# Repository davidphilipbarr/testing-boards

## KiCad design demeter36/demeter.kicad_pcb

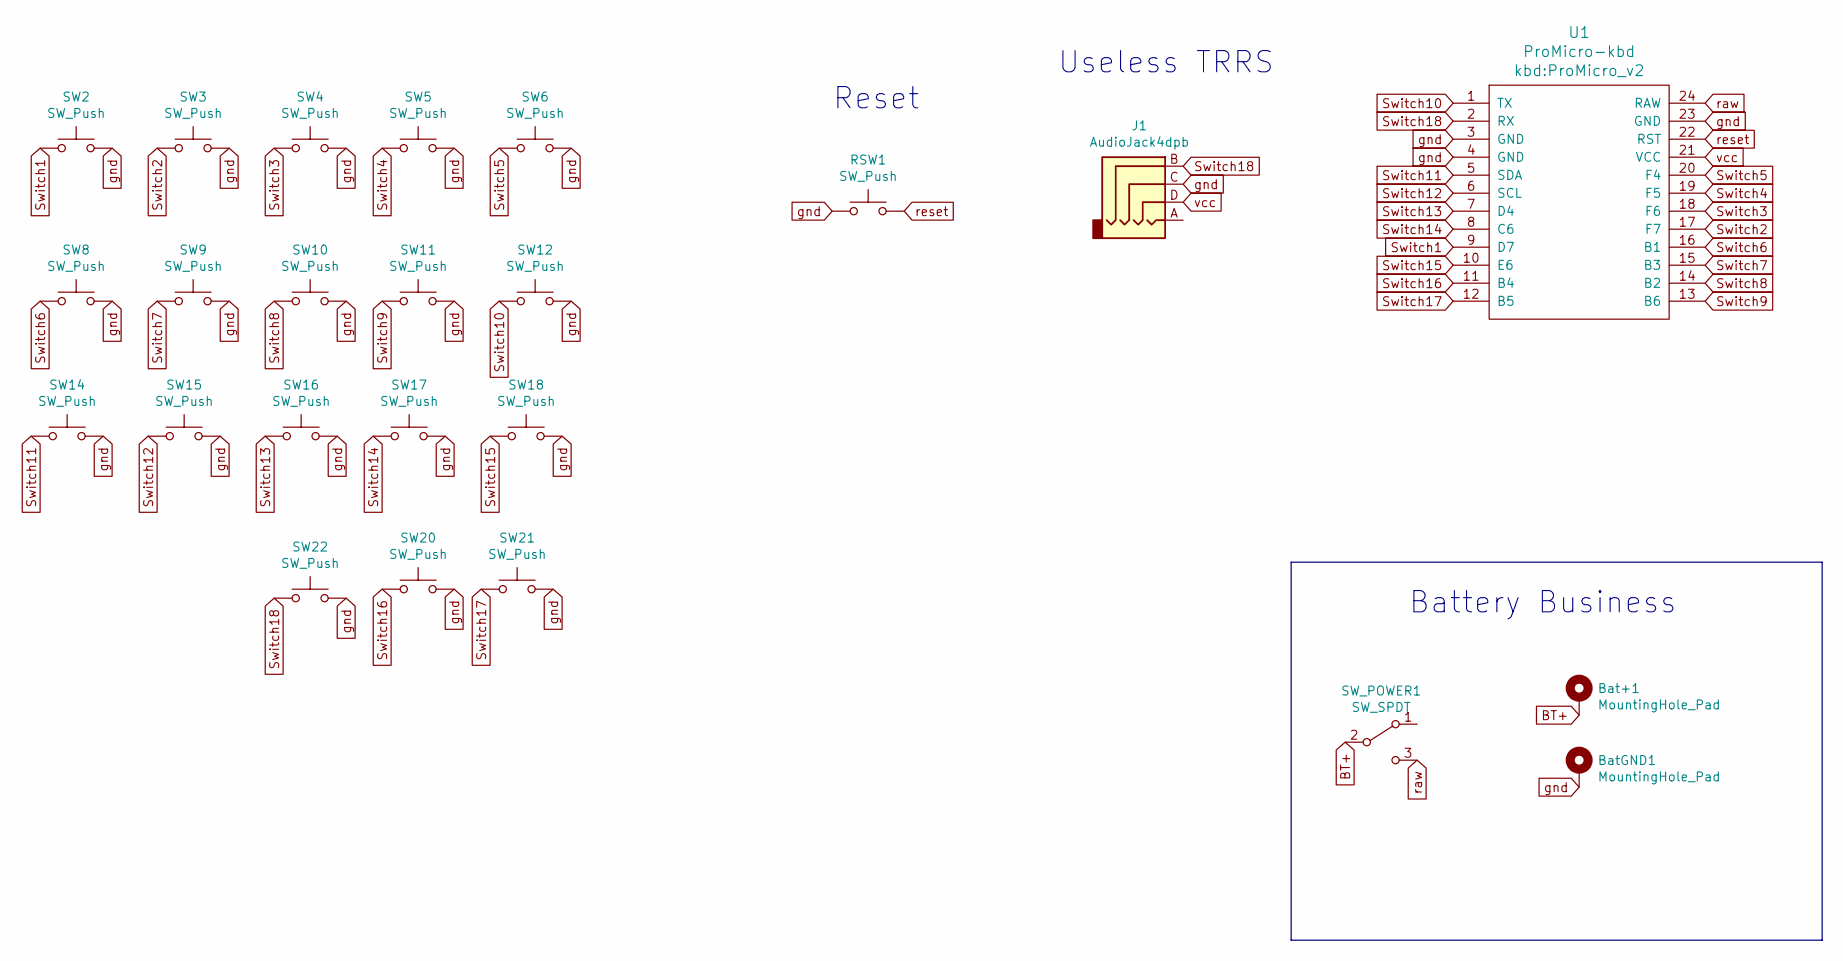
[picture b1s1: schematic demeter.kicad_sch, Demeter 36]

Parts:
Bat+1: MountingHole_Pad; 1pin_conn
BatGND1: MountingHole_Pad; 1pin_conn
J1: AudioJack4dpb; MJ-4PP-9
RSW1: SW_Push; ResetSW
SW2, SW3, SW4, SW5, SW6, SW8, SW9, SW10, SW11, SW12, SW14, SW15, SW16, SW17, SW18, SW20, SW21, SW22: SW_Push; SW_PG1350_rev_DPB
SW_POWER1: SW_SPDT; SPDT_C128955
U1: ProMicro-kbd; ProMicro_v2

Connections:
BT+: Bat+1.1, SW_POWER1.2 (B), U1.27; also elsewhere on the board
Switch1: SW2.1, U1.9 (D7)
Switch2: SW3.1, U1.17 (F7)
Switch3: SW4.1, U1.18 (F6)
Switch4: SW5.1, U1.19 (F5)
Switch5: SW6.1, U1.20 (F4)
Switch6: SW8.1, U1.16 (B1)
Switch7: SW9.1, U1.15 (B3)
Switch8: SW10.1, U1.14 (B2)
Switch9: SW11.1, U1.13 (B6)
Switch10: SW12.1, U1.1 (TX)
Switch11: SW14.1, U1.5 (SDA)
Switch12: SW15.1, U1.6 (SCL)
Switch13: SW16.1, U1.7 (D4)
Switch14: SW17.1, U1.8 (C6)
Switch15: SW18.1, U1.10 (E6)
Switch16: SW20.1, U1.11 (B4)
Switch17: SW21.1, U1.12 (B5)
Switch18: J1.B, SW22.1, U1.2 (RX); also elsewhere on the board
gnd: BatGND1.1, J1.C, RSW1.1, SW2.2, SW3.2, SW4.2, SW5.2, SW6.2, SW8.2, SW9.2, SW10.2, SW11.2, SW12.2, SW14.2, SW15.2, SW16.2, SW17.2, SW18.2, SW20.2, SW21.2, SW22.2, U1.3 (GND), U1.4 (GND), U1.23 (GND); also elsewhere on the board
raw: SW_POWER1.3 (C), U1.24 (RAW); also elsewhere on the board
reset: RSW1.2, U1.22 (RST)
vcc: J1.D, U1.21 (VCC)

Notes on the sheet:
Reset
Battery Business
Useless TRRS

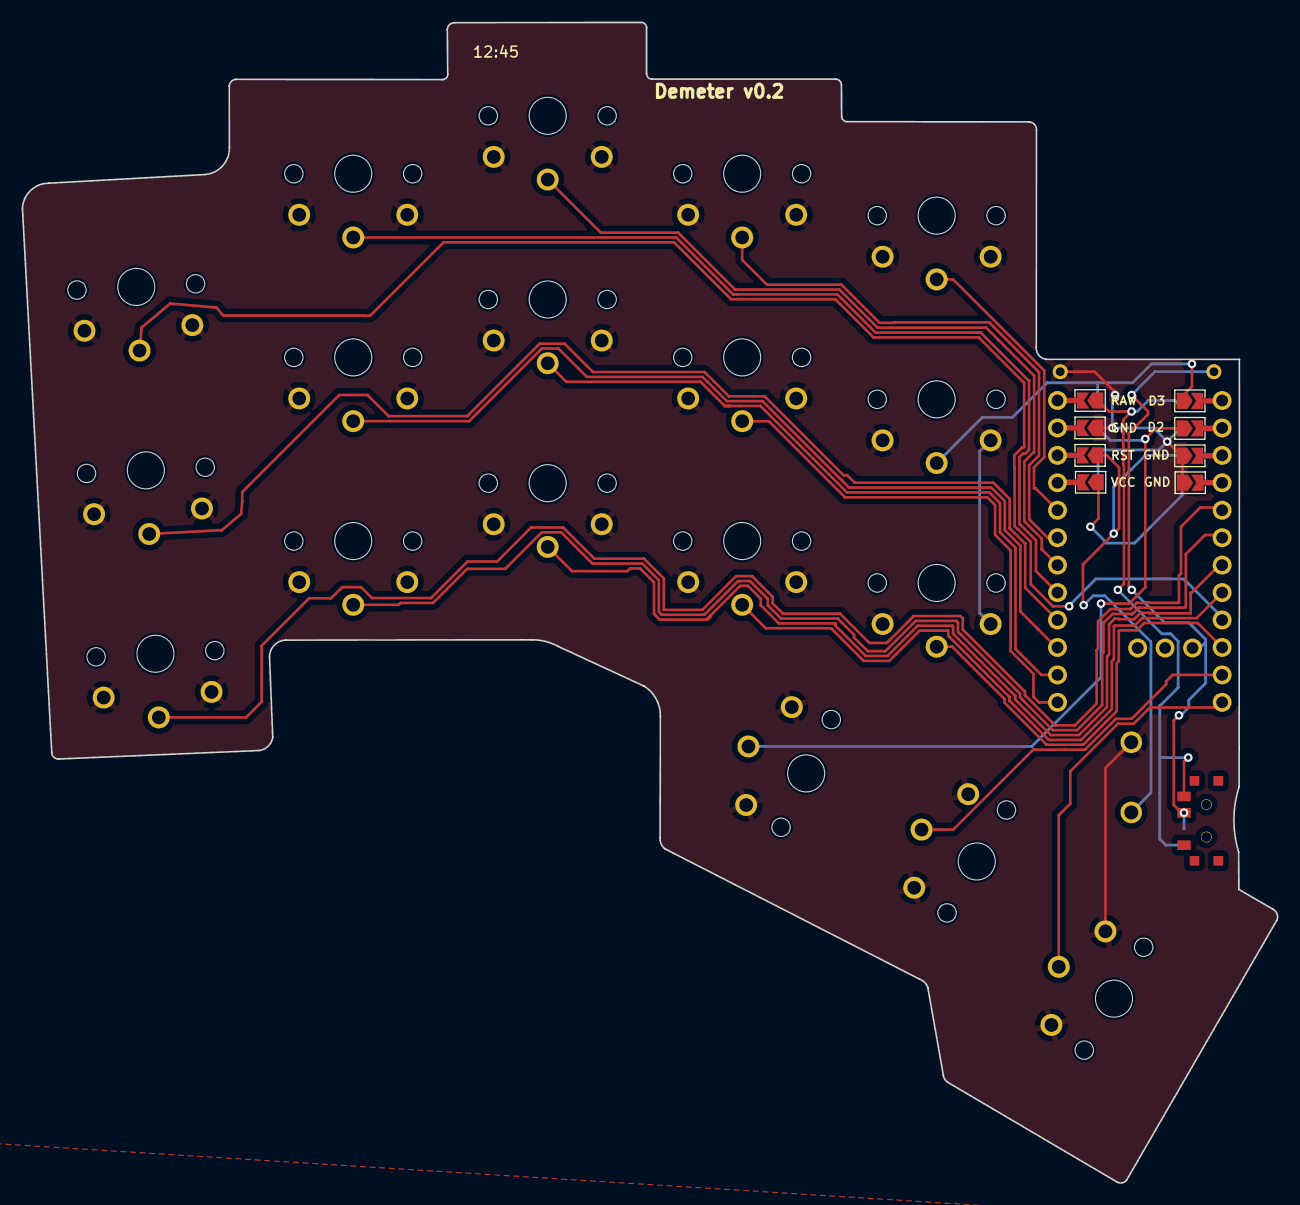
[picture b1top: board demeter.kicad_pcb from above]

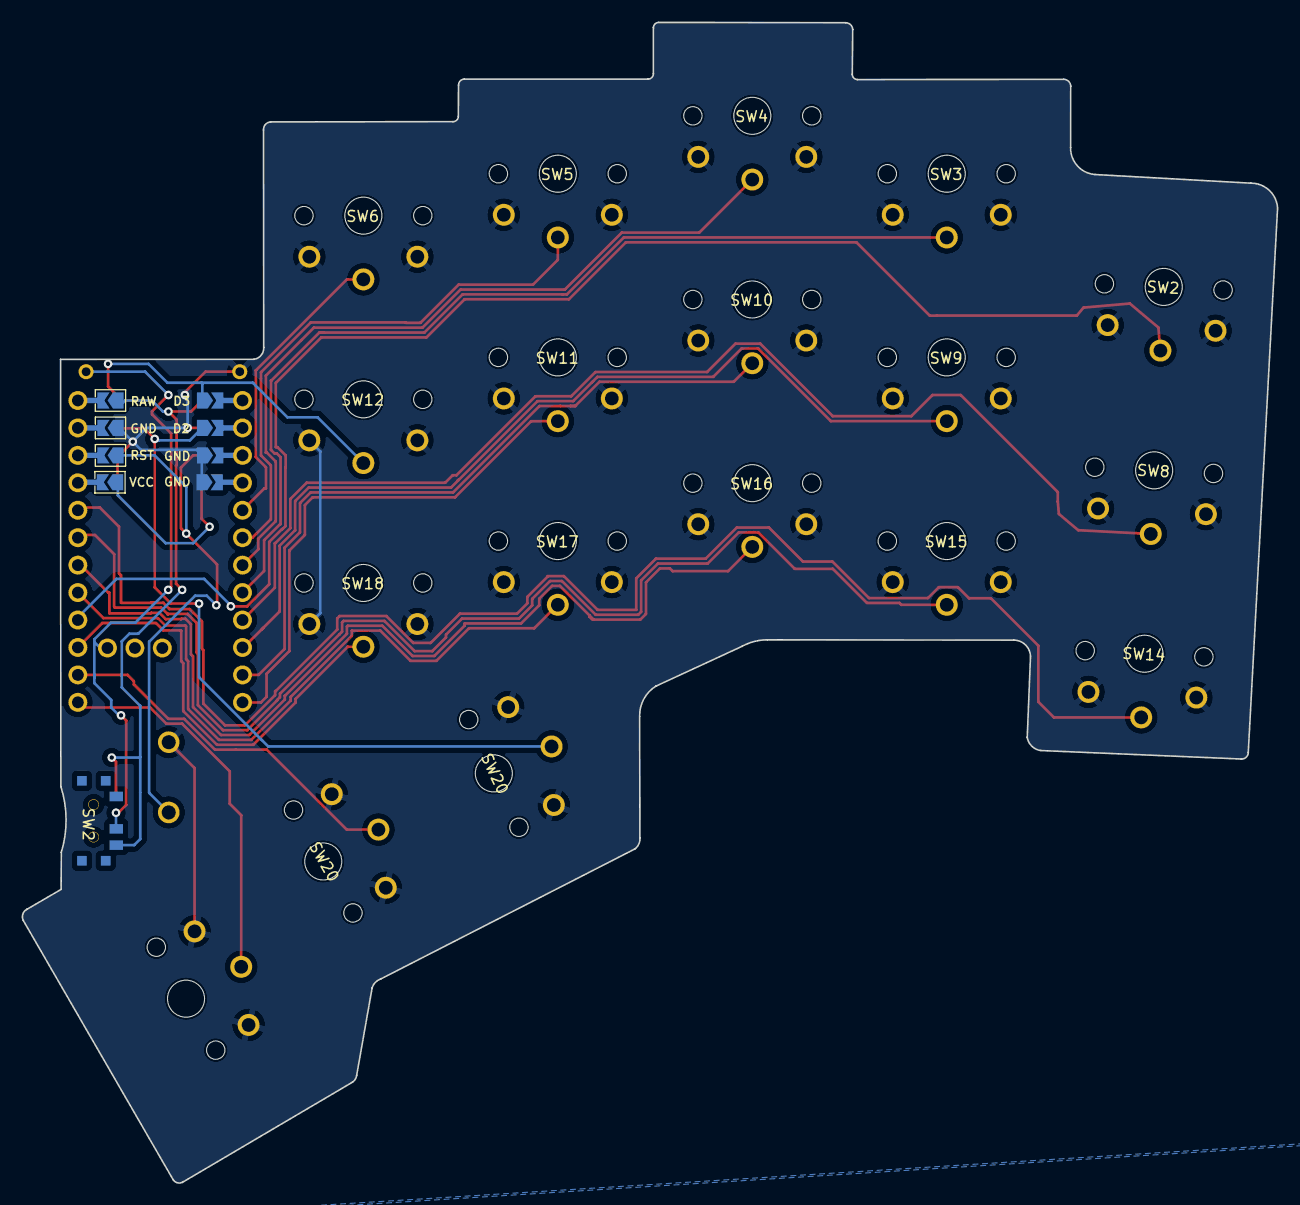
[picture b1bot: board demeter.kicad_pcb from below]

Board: 2 copper layers, 116.2 x 107.4 mm, 24 parts (2 on the bottom side), 22 nets.

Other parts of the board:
SW2#2: SW_SPDT; SPDT_C128955r
SW20#2: SW_Push; SW_PG1350_rev_DPB2.2

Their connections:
BT+: SW2#2.2; also elsewhere on the board
Switch18: SW20#2.1; also elsewhere on the board
gnd: SW20#2.2; also elsewhere on the board
raw: SW2#2.3; also elsewhere on the board

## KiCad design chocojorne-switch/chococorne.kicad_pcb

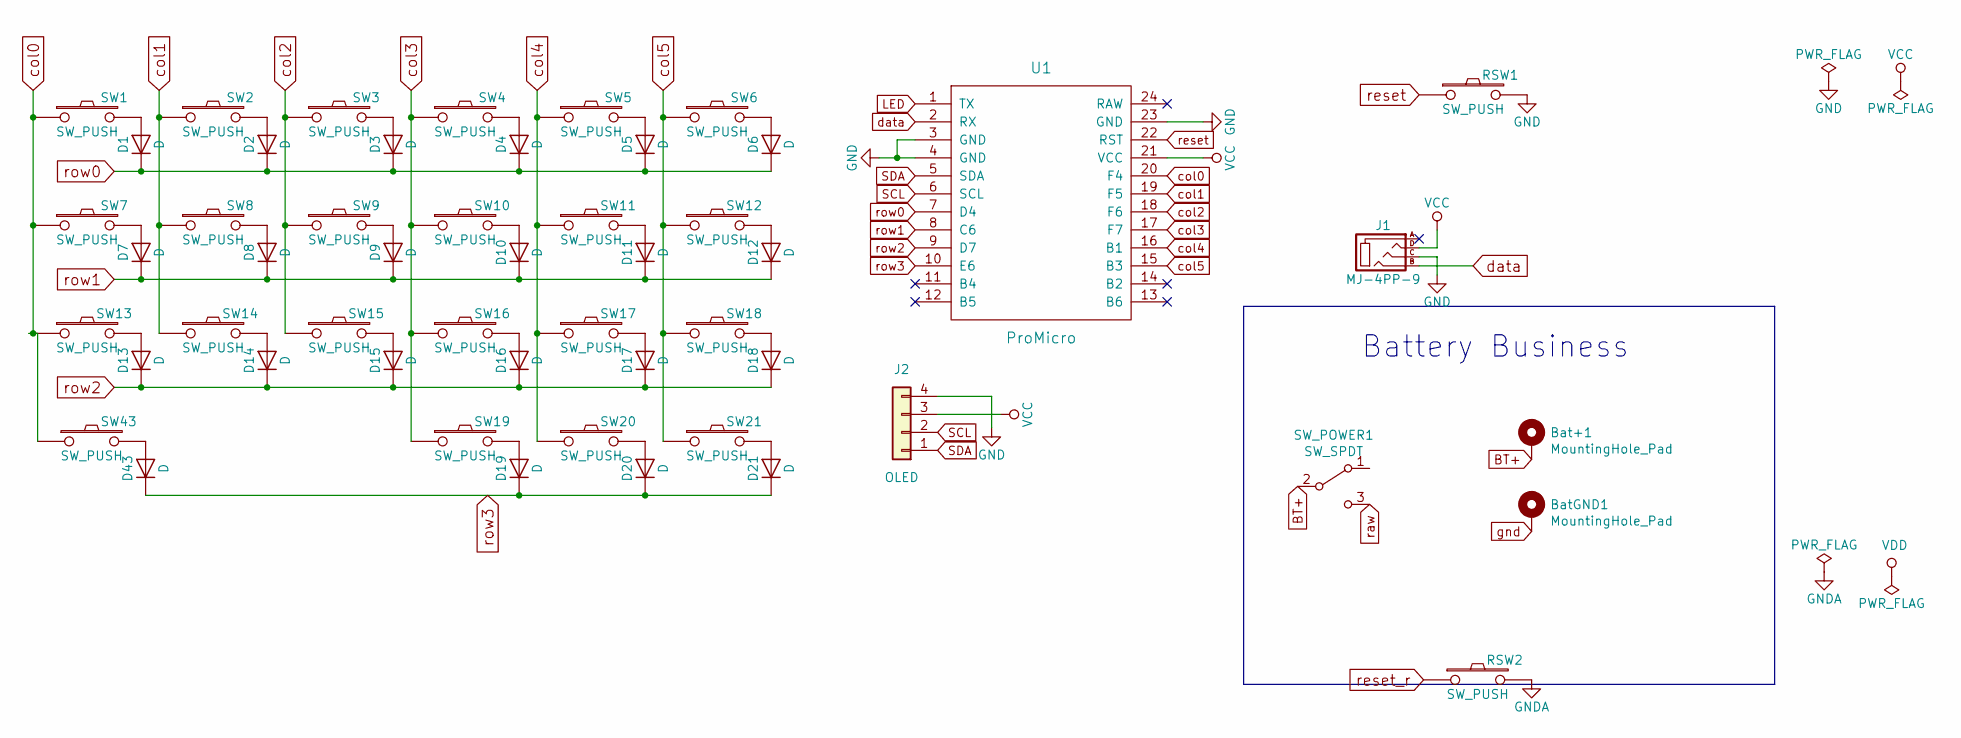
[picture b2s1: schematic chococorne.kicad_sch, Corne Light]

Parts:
Bat+1: MountingHole_Pad; 1pin_conn
BatGND1: MountingHole_Pad; 1pin_conn
D1, D2, D3, D4, D5, D6, D7, D8, D9, D10, D11, D12, D13, D14, D15, D16, D17, D18, D19, D20, D21, D43: D; D3_TH
J1: MJ-4PP-9; MJ-4PP-9_1side
J2: OLED; OLED_1side
RSW1, RSW2: SW_PUSH; ResetSW_1side
SW1, SW2, SW3, SW4, SW5, SW6, SW7, SW8, SW9, SW10, SW11, SW12, SW13, SW14, SW15, SW16, SW17, SW18, SW19, SW20, SW43: SW_PUSH; CherryMX_Choc_1u
SW21: SW_PUSH; CherryMX_Choc_1.5u
SW_POWER1: SW_SPDT; SPDT_C128955
U1: ProMicro; ProMicro_v2_1side

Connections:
BT+: Bat+1.1, SW_POWER1.2 (B); also elsewhere on the board
GND: J1.C, J2.4, RSW1.2, U1.3 (GND), U1.4 (GND), U1.23 (GND); also elsewhere on the board
LED: U1.1 (TX)
unnamed: D1.2 (A), SW1.2
unnamed: D2.2 (A), SW2.2
unnamed: D3.2 (A), SW3.2
unnamed: D4.2 (A), SW4.2
unnamed: D5.2 (A), SW5.2
unnamed: D6.2 (A), SW6.2
unnamed: D7.2 (A), SW7.2
unnamed: D8.2 (A), SW8.2
unnamed: D9.2 (A), SW9.2
unnamed: D10.2 (A), SW10.2
unnamed: D11.2 (A), SW11.2
unnamed: D12.2 (A), SW12.2
unnamed: D13.2 (A), SW13.2
unnamed: D14.2 (A), SW14.2
unnamed: D15.2 (A), SW15.2
unnamed: D16.2 (A), SW16.2
unnamed: D17.2 (A), SW17.2
unnamed: D18.2 (A), SW18.2
unnamed: D19.2 (A), SW19.2
unnamed: D20.2 (A), SW20.2
unnamed: D21.2 (A), SW21.2
unnamed: D43.2 (A), SW43.2
SCL: J2.2, U1.6 (SCL); also elsewhere on the board
SDA: J2.1, U1.5 (SDA); also elsewhere on the board
VCC: J1.D, J2.3, U1.21 (VCC); also elsewhere on the board
col0: SW1.1, SW7.1, SW13.1, SW43.1, U1.20 (F4)
col1: SW2.1, SW8.1, SW14.1, U1.19 (F5)
col2: SW3.1, SW9.1, SW15.1, U1.18 (F6)
col3: SW4.1, SW10.1, SW16.1, SW19.1, U1.17 (F7)
col4: SW5.1, SW11.1, SW17.1, SW20.1, U1.16 (B1)
col5: SW6.1, SW12.1, SW18.1, SW21.1, U1.15 (B3)
data: J1.B, U1.2 (RX)
gnd: BatGND1.1
raw: SW_POWER1.3 (C); also elsewhere on the board
reset: RSW1.1, U1.22 (RST)
row0: D1.1 (K), D2.1 (K), D3.1 (K), D4.1 (K), D5.1 (K), D6.1 (K), U1.7 (D4)
row1: D7.1 (K), D8.1 (K), D9.1 (K), D10.1 (K), D11.1 (K), D12.1 (K), U1.8 (C6)
row2: D13.1 (K), D14.1 (K), D15.1 (K), D16.1 (K), D17.1 (K), D18.1 (K), U1.9 (D7)
row3: D19.1 (K), D20.1 (K), D21.1 (K), D43.1 (K), U1.10 (E6)

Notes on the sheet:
Battery Business

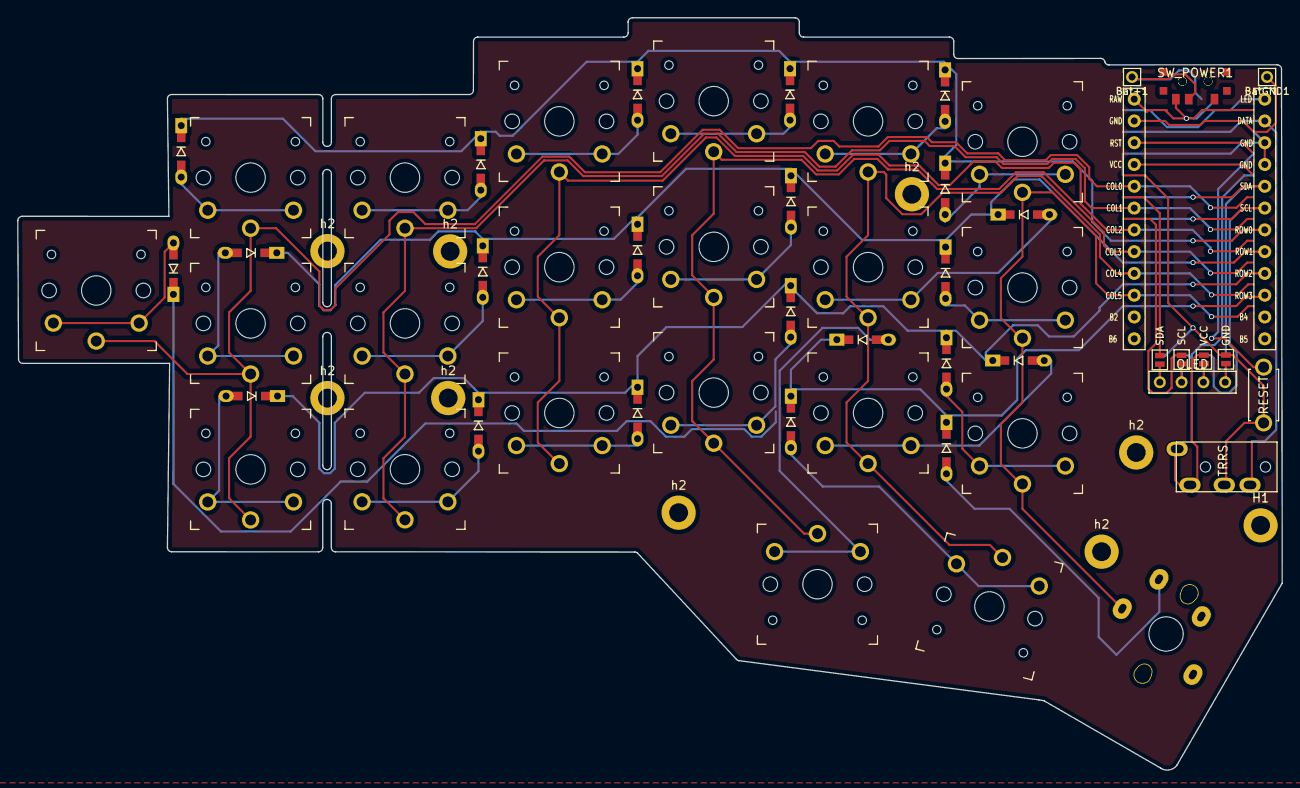
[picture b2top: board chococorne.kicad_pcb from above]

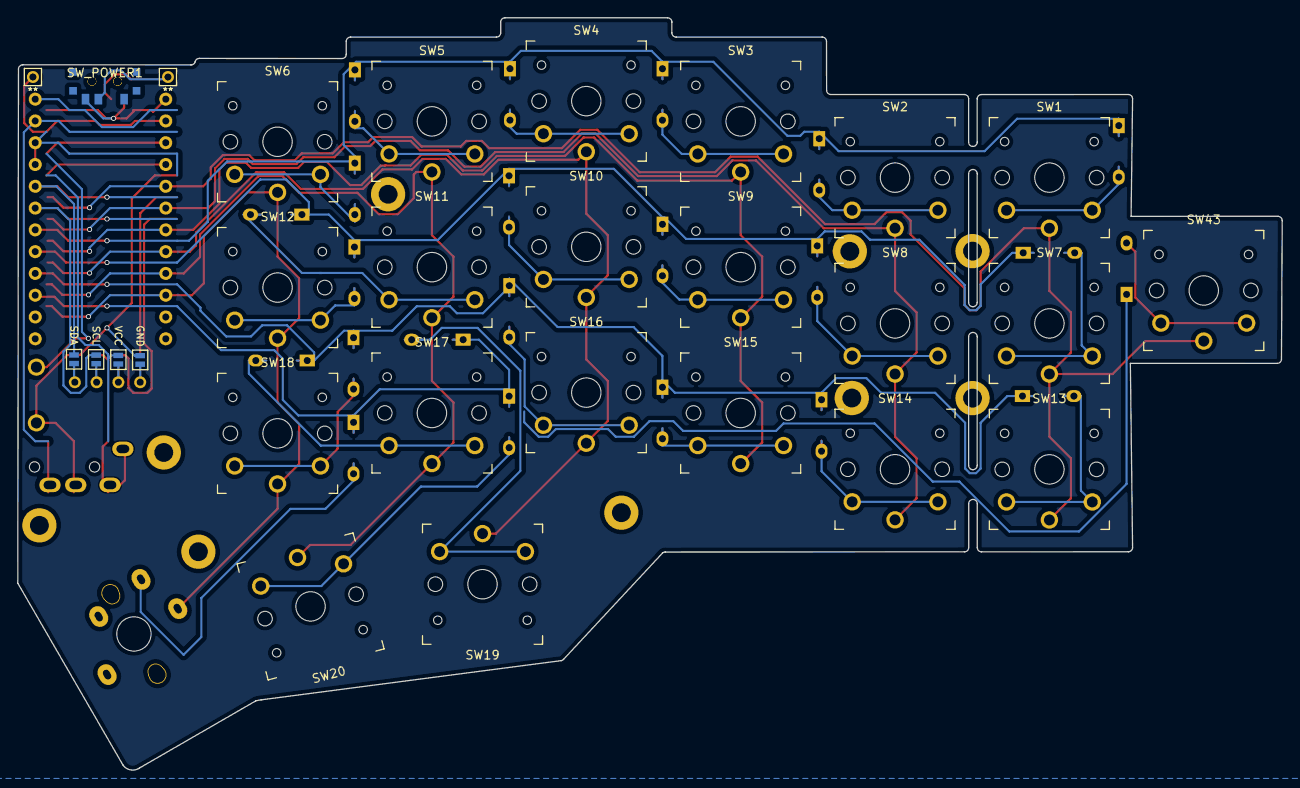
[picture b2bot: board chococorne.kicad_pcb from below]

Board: 2 copper layers, 147.4 x 87.7 mm, 69 parts (5 on the bottom side), 44 nets.

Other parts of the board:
H1: h1; LEGO_HOLE
JP6, JP61: SDA; Jumper
JP62, JP68: GND; Jumper
JP63, JP66: SCL; Jumper
JP64, JP65: VCC; Jumper
SW_POWER1#2: SW_SPDT; SPDT_C128955
h2, h2#2, h2#3, h2#4, h2#5, h2#6, h2#7, h2#8: h2; LEGO_HOLE

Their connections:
BT+: SW_POWER1#2.2 (B); also elsewhere on the board
GND: JP62.1, JP68.1; also elsewhere on the board
unnamed: JP65.2, JP66.2
unnamed: JP6.2, JP68.2
unnamed: JP63.2, JP64.2
unnamed: JP61.2, JP62.2
SCL: JP63.1, JP66.1; also elsewhere on the board
SDA: JP6.1, JP61.1; also elsewhere on the board
VCC: JP64.1, JP65.1; also elsewhere on the board
raw: SW_POWER1#2.3 (C); also elsewhere on the board

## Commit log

2022-03-03 sweep with no trrs
2022-04-14 add sweep version for gateron low profile switches
2022-04-16 simplify footprint
2022-04-17 routing
2022-04-19 trrs only one way
2022-07-20 add some silks tweak some angles
2022-07-20 actually align the switches
2022-07-20 do not have a silk disaster, do not have a silk disaster
    do not have a silk disaster, do not have a silk disaster, do not have a silk disaster, do not have a silk disaster, do not have a silk disaster, do not have a silk disaster, do not have a silk disast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
2022-07-20 tweaks
2022-07-21 try to be subtle
2022-07-24 it is what it is
2022-07-25 the neatening
2022-08-03 add xaio sweep thing
2022-08-08 move some diodes
2022-08-08 what we got
2022-08-08 changes based on kyek's feedback
    changes from @duckyb
2022-08-08 Fix DRC on gogo-corne
2022-08-09 sort of clean up
2022-09-04 fix switch placement
2022-09-07 thumb nudge
2022-11-25 sweep with jst
2023-01-06 an image
2024-02-01 36 key demeter
2024-02-01 Quick screenshot
2024-02-01 move third thumb a bit
2024-04-28 Fisrt effort at all choc v1 hypergolic, the shame.
2024-04-28 add awkward screenshot
